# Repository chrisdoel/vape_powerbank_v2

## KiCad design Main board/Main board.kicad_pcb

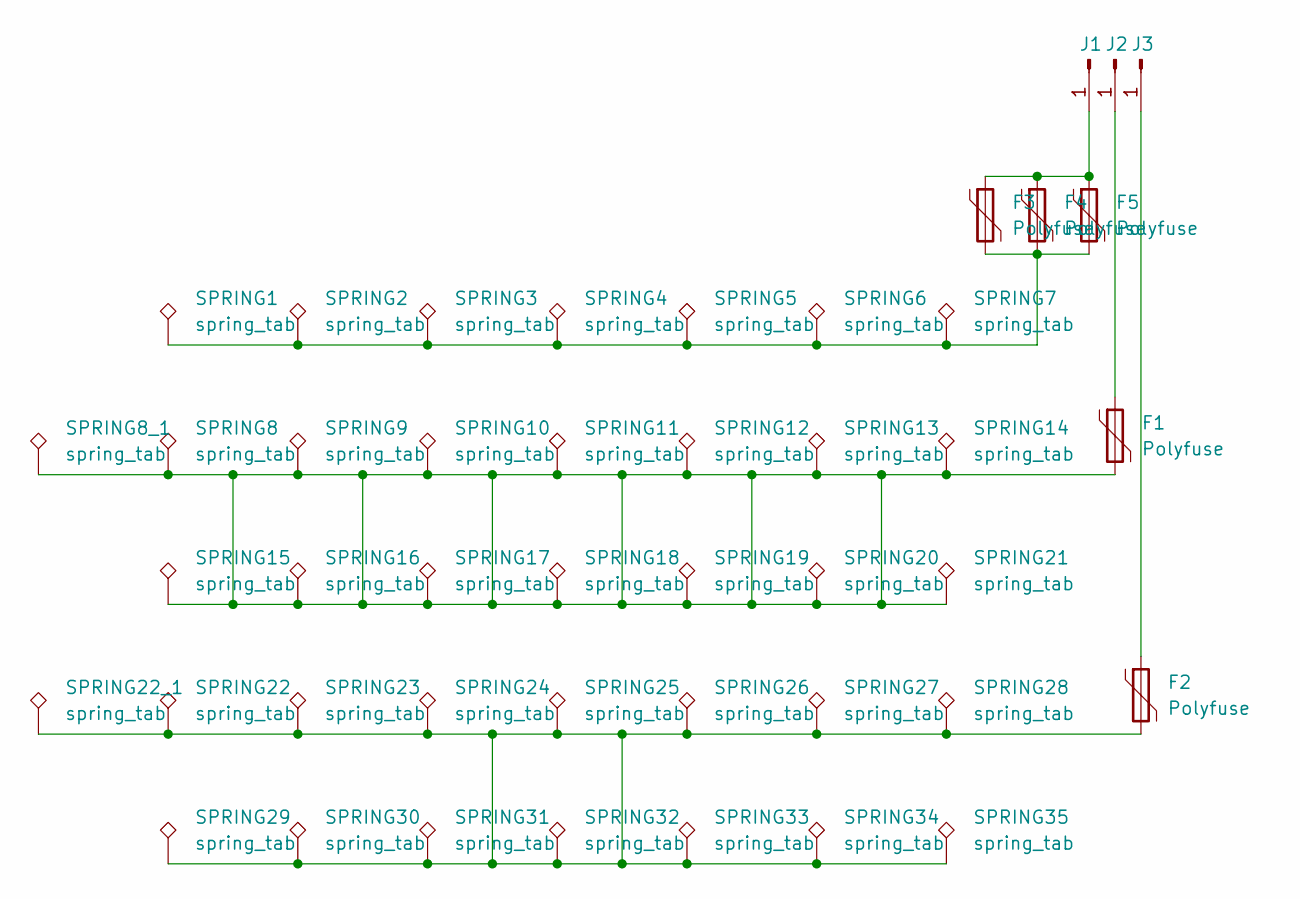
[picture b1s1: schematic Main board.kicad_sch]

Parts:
F1, F2, F3, F4, F5: Polyfuse; Fuse_1812_4532Metric
J1, J2, J3: Conn_01x01_Pin; SMD_spring_clamp_connector_1x1
SPRING1, SPRING2, SPRING3, SPRING4, SPRING5, SPRING6, SPRING7, SPRING8, SPRING8_1, SPRING9, SPRING10, SPRING11, SPRING12, SPRING13, SPRING14, SPRING15, SPRING16, SPRING17, SPRING18, SPRING19, SPRING20, SPRING21, SPRING22, SPRING22_1, SPRING23, SPRING24, SPRING25, SPRING26, SPRING27, SPRING28, SPRING29, SPRING30, SPRING31, SPRING32, SPRING33, SPRING34, SPRING35: spring_tab

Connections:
unnamed: F1.2, SPRING8.1, SPRING8_1.1, SPRING9.1, SPRING10.1, SPRING11.1, SPRING12.1, SPRING13.1, SPRING14.1, SPRING15.1, SPRING16.1, SPRING17.1, SPRING18.1, SPRING19.1, SPRING20.1, SPRING21.1
unnamed: F2.2, SPRING22.1, SPRING22_1.1, SPRING23.1, SPRING24.1, SPRING25.1, SPRING26.1, SPRING27.1, SPRING28.1, SPRING29.1, SPRING30.1, SPRING31.1, SPRING32.1, SPRING33.1, SPRING34.1, SPRING35.1
unnamed: F3.2, F4.2, F5.2, SPRING1.1, SPRING2.1, SPRING3.1, SPRING4.1, SPRING5.1, SPRING6.1, SPRING7.1
unnamed: F3.1, F4.1, F5.1, J1.1
unnamed: F1.1, J2.1
unnamed: F2.1, J3.1

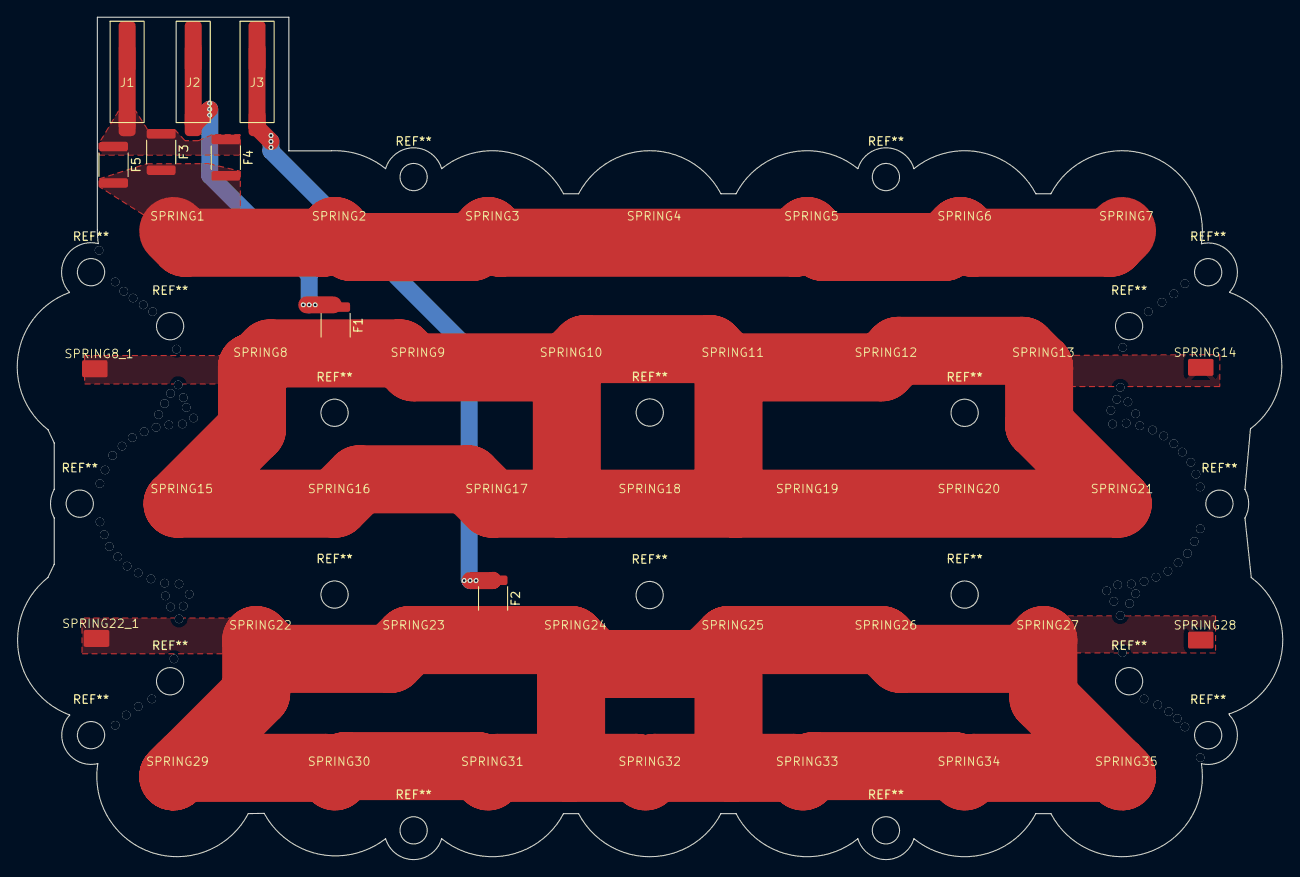
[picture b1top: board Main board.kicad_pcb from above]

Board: 2 copper layers, 148.7 x 99.0 mm, 45 parts (0 on the bottom side), 6 nets.

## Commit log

2024-09-11 created schematic and spring footprint
2024-09-15 Created breakable symmetrical version
